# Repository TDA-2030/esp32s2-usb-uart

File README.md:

# ESP32S2-USB-UART

USB to UART board by ESP32-S2

## Feature

- [x] USB to UART
- [x] PCB size: 30mm x 14mm
- [x] All output with ESD protection
- [x] 3 LEDs
- [x] LEDs to indicate UART signal
- [x] 3.3V output
- [x] Either USBA or Type-C plug
- [ ] Auto download for ESP series chips
- [ ] Wireless connecting

## Pin definition

| 1(TCK) | 10(TX) |
| ------ | ------ |
| 2(TDI) | 9(RX)  |
| 3(TDO) | 8(EN)  |
| 4(TMS) | 7(IO0) |
| 5(3V3) | 6(GND) |

## Preview image

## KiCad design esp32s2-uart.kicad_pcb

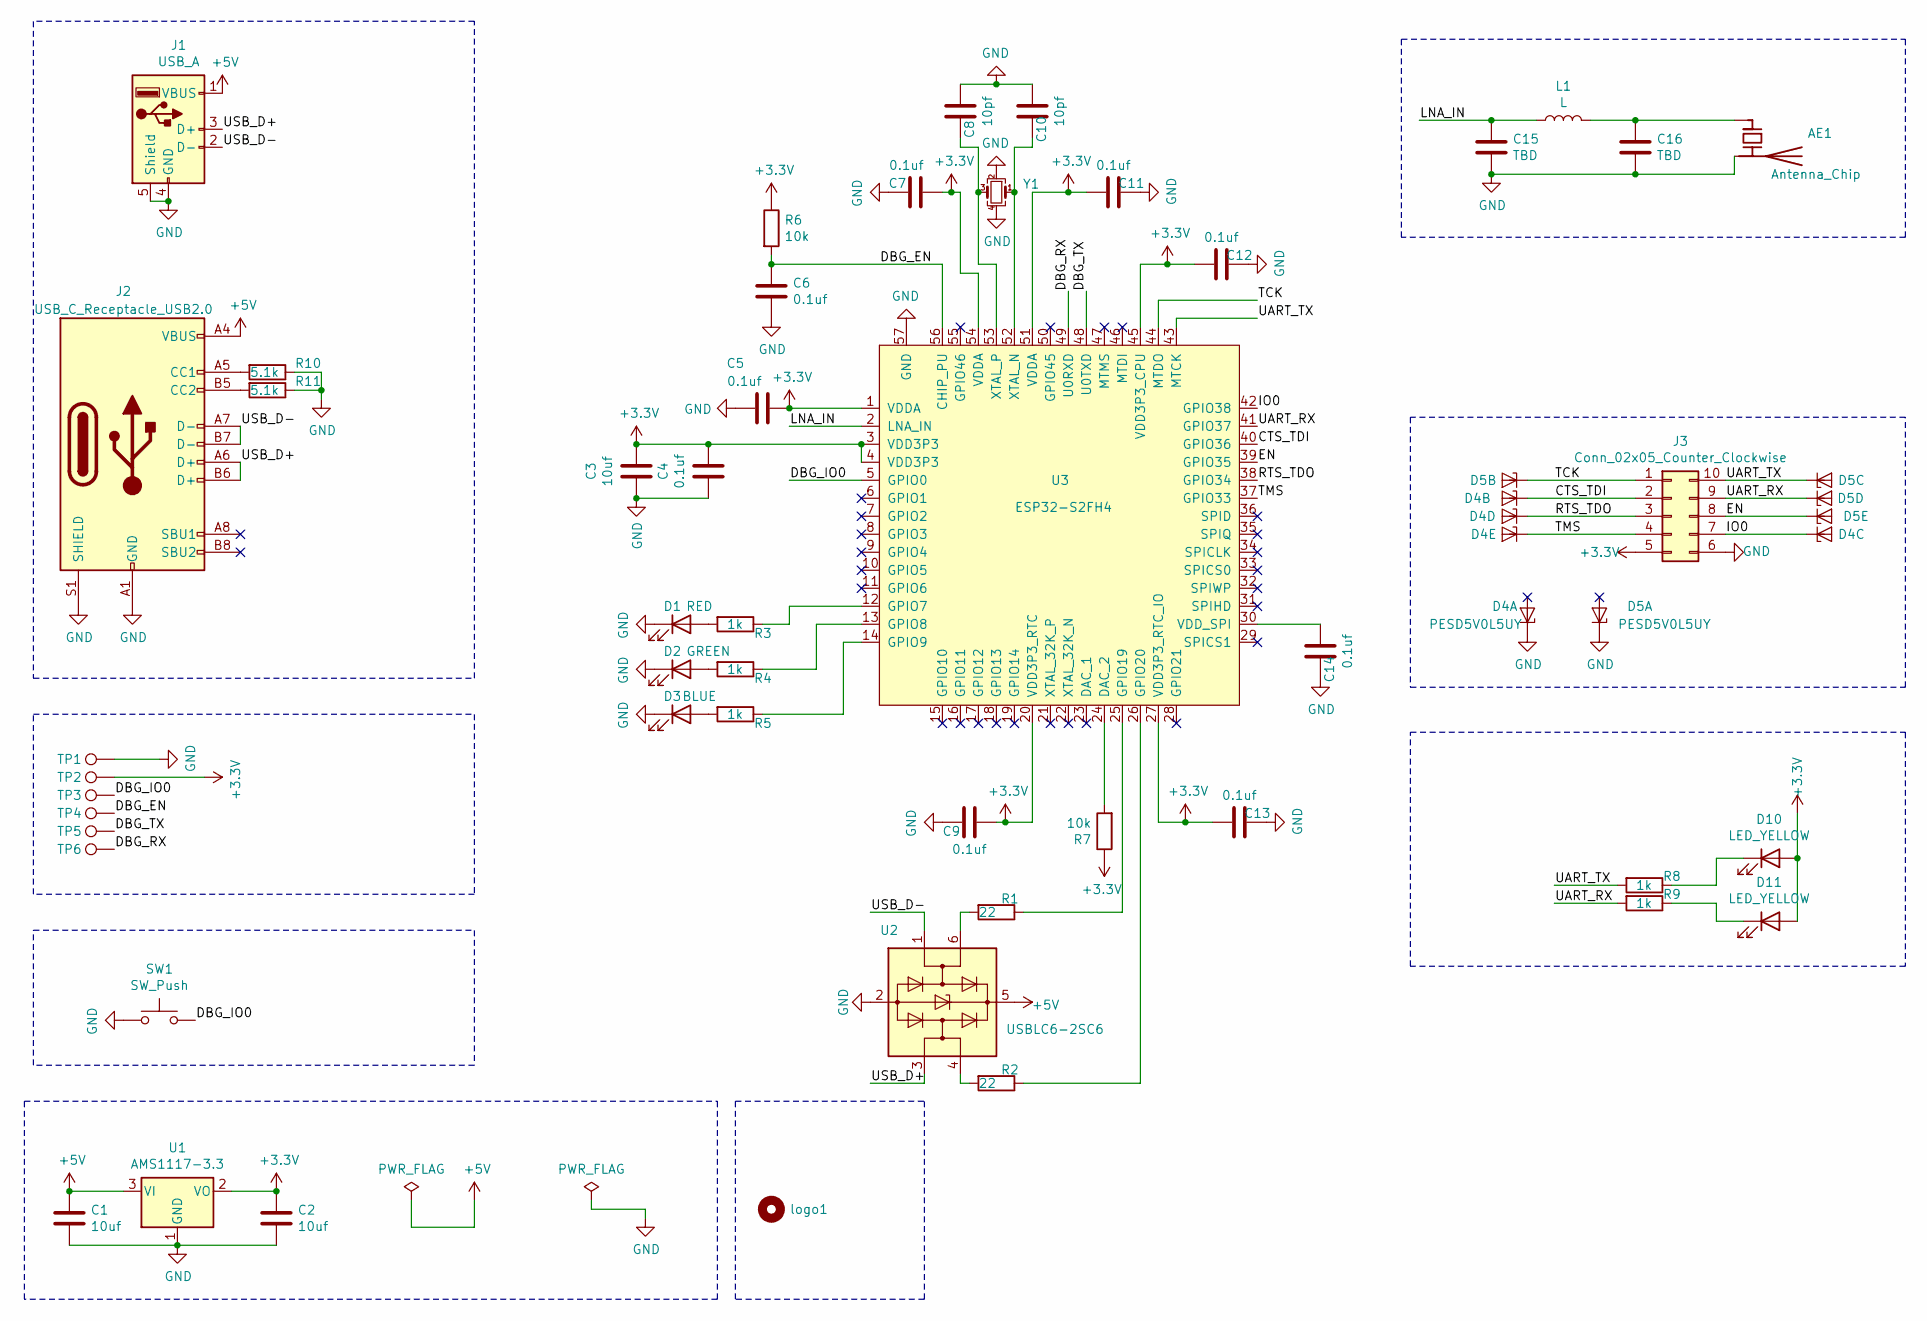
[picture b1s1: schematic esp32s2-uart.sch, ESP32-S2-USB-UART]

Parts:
AE1: Antenna_Chip; Johanson_2450AT43F0100
C1, C2, C3: 10uf; C_0603_1608Metric
C4, C5, C6, C7, C9, C11, C12, C13, C14: 0.1uf; C_0402_1005Metric
C8, C10: 10pf; C_0402_1005Metric
C15, C16: TBD; C_0402_1005Metric
D1: RED; LED_0603_1608Metric
D2: GREEN; LED_0603_1608Metric
D3: BLUE; LED_0603_1608Metric
D4, D5: PESD5V0L5UY; SOT-363_SC-70-6
D10, D11: LED_YELLOW; LED_0603_1608Metric
J1: USB_A; USB_A_CNCTech_1001-011-01101_Horizontal
J2: USB_C_Receptacle_USB2.0; USB_C_Receptacle
J3: Conn_02x05_Counter_Clockwise; Header_2x5_pin
L1: L; L_0402_1005Metric
R1, R2: 22; R_0402_1005Metric
R3, R4, R5, R8, R9: 1k; R_0402_1005Metric
R6, R7: 10k; R_0402_1005Metric
R10, R11: 5.1k; R_0402_1005Metric
SW1: SW_Push; button
TP1, TP2, TP3, TP4, TP5, TP6: TestPoint; TestPoint_Pad_D1.0mm
U1: AMS1117-3.3; SOT-223-3_TabPin2
U2: USBLC6-2SC6; SOT-23-6
U3: ESP32-S2FH4; QFN-56-1EP_7x7mm_P0.4mm_EP5.6x5.6mm
Y1: Crystal_GND24_Small; Crystal_SMD_EuroQuartz_MT-4Pin_3.2x2.5mm
logo1: logo; ESP-USB-Bridge

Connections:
+3V3: C2.2, C3.1, C4.1, C5.1, C7.1, C9.2, C11.2, C12.2, C13.2, D10.2 (A), D11.2 (A), J3.5, R6.1, R7.1, TP2.1, U1.2 (VO), U3.1 (VDDA), U3.3 (VDD3P3), U3.4 (VDD3P3), U3.20 (VDD3P3_RTC), U3.27 (VDD3P3_RTC_IO), U3.45 (VDD3P3_CPU), U3.51 (VDDA), U3.54 (VDDA)
+5V: C1.2, J1.1 (VBUS), J2.A4 (VBUS), J2.A9 (VBUS), J2.B4 (VBUS), J2.B9 (VBUS), U1.3 (VI), U2.5 (VBUS)
/CTS_TDI: D4.3 (K2), J3.2, U3.40 (GPIO36)
/DBG_EN: C6.1, R6.2, TP4.1, U3.56 (CHIP_PU)
/DBG_IO0: SW1.2, TP3.1, U3.5 (GPIO0)
/DBG_RX: TP6.1, U3.49 (U0RXD)
/DBG_TX: TP5.1, U3.48 (U0TXD)
/EN: D5.6 (K5), J3.8, U3.39 (GPIO35)
/IO0: D4.4 (K3), J3.7, U3.42 (GPIO38)
/LNA_IN: C15.1, L1.1, U3.2 (LNA_IN)
/RTS_TDO: D4.5 (K4), J3.3, U3.38 (GPIO34)
/TCK: D5.3 (K2), J3.1, U3.44 (MTDO)
/TMS: D4.6 (K5), J3.4, U3.37 (GPIO33)
/UART_RX: D5.5 (K4), J3.9, R9.2, U3.41 (GPIO37)
/UART_TX: D5.4 (K3), J3.10, R8.2, U3.43 (MTCK)
/USB_D+: J1.3 (D+), J2.A6 (D+), J2.B6 (D+), U2.3 (I/O2)
/USB_D-: J1.2 (D-), J2.A7 (D-), J2.B7 (D-), U2.1 (I/O1)
GND: AE1.2 (PCB_Trace), C1.1, C2.1, C3.2, C4.2, C5.2, C6.2, C7.2, C8.2, C9.1, C10.2, C11.1, C12.1, C13.1, C14.1, C15.2, C16.2, D1.1 (K), D2.1 (K), D3.1 (K), D4.1 (K1), D5.1 (K1), J1.4 (GND), J1.5 (Shield), J2.A1 (GND), J2.A12 (GND), J2.B1 (GND), J2.B12 (GND), J2.S1 (SHIELD), J3.6, R10.1, R11.1, SW1.1, TP1.1, U1.1 (GND), U2.2 (GND), U3.57 (GND), Y1.2, Y1.4
unnamed: AE1.1 (FEED), C16.1, L1.2
unnamed: C8.1, U3.53 (XTAL_P), Y1.3
unnamed: C10.1, U3.52 (XTAL_N), Y1.1
unnamed: C14.2, U3.30 (VDD_SPI)
unnamed: D1.2 (A), R3.2
unnamed: D2.2 (A), R4.2
unnamed: D3.2 (A), R5.2
unnamed: D10.1 (K), R8.1
unnamed: D11.1 (K), R9.1
unnamed: J2.A5 (CC1), R10.2
unnamed: J2.B5 (CC2), R11.2
unnamed: R1.1, U3.25 (GPIO19)
unnamed: R1.2, U2.6 (I/O1)
unnamed: R2.1, U3.26 (GPIO20)
unnamed: R2.2, U2.4 (I/O2)
unnamed: R3.1, U3.12 (GPIO7)
unnamed: R4.1, U3.13 (GPIO8)
unnamed: R5.1, U3.14 (GPIO9)
unnamed: R7.2, U3.24 (DAC_2)

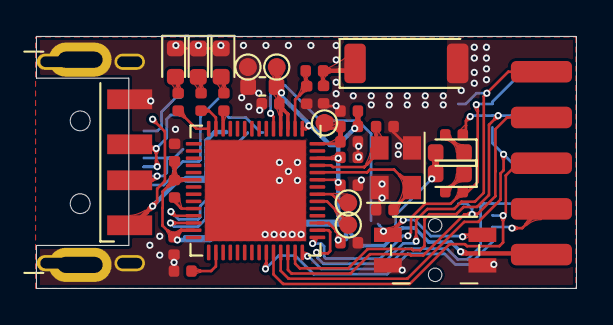
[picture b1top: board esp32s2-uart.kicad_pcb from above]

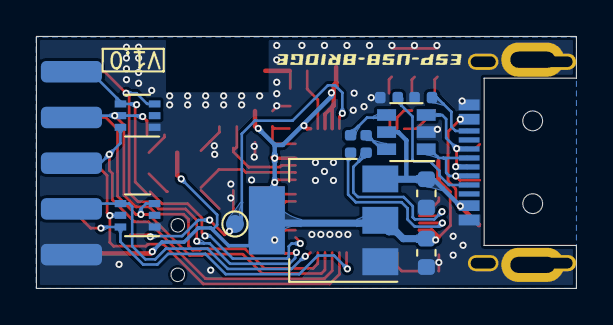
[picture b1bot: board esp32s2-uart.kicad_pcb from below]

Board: 2 copper layers, 30.0 x 14.0 mm, 51 parts (13 on the bottom side), 37 nets.

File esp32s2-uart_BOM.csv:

"Comment","Description","Designator","Footprint","LibRef","Pins","Quantity","PartNumber","url",
"10uf","desc","C3,","C_0603_1608Metric","libref","2","1","","",
"0.1uf","desc","C4,C5,C6,C7,C9,C11,C12,C13,C14,","C_0402_1005Metric","libref","2","9","","",
"10pf","desc","C8,C10,","C_0402_1005Metric","libref","2","2","","",
"TBD","desc","C15,C16,","C_0402_1005Metric","libref","2","2","","",
"RED","desc","D1,","LED_0603_1608Metric","libref","2","1","","",
"GREEN","desc","D2,","LED_0603_1608Metric","libref","2","1","","",
"BLUE","desc","D3,","LED_0603_1608Metric","libref","2","1","","",
"LED_YELLOW","desc","D10,D11,","LED_0603_1608Metric","libref","2","2","","",
"Conn_02x05_Counter_Clockwise","desc","J3,","Header_2x5_pin","libref","10","1","","",
"L","desc","L1,","L_0402_1005Metric","libref","2","1","","",
"1k","desc","R3,R4,R5,R8,R9,","R_0402_1005Metric","libref","2","5","","",
"10k","desc","R6,R7,","R_0402_1005Metric","libref","2","2","","",
"ESP32-S2FH4","desc","U3,","QFN-56-1EP_7x7mm_P0.4mm_EP5.6x5.6mm","libref","73","1","","",
"Crystal_GND24_Small","desc","Y1,","Crystal_SMD_EuroQuartz_MT-4Pin_3.2x2.5mm","libref","4","1","","",
"Antenna_Chip","desc","AE1,","Johanson_2450AT43F0100","libref","2","1","","",
"TestPoint","desc","TP1,TP2,TP4,TP5,TP6,","TestPoint_Pad_D1.0mm","libref","1","5","","",
"10uf","desc","C1,C2,","C_0603_1608Metric","libref","2","2","","",
"PESD5V0L5UY","desc","D4,D5,","SOT-363_SC-70-6","libref","6","2","","",
"22","desc","R1,R2,","R_0402_1005Metric","libref","2","2","","",
"5.1k","desc","R10,R11,","R_0402_1005Metric","libref","2","2","","",
"AMS1117-3.3","desc","U1,","SOT-223-3_TabPin2","libref","4","1","","",
"USBLC6-2SC6","desc","U2,","SOT-23-6","libref","6","1","","",
"TestPoint","desc","TP3,","TestPoint_Pad_D1.0mm","libref","1","1","","",
"logo","desc","logo1,","ESP-USB-Bridge","libref","0","1","","",
"Through Hole Items ",
"USB_A","desc","J1,","USB_A_CNCTech_1001-011-01101_Horizontal","libref","8","1","","",
"SW_Push","desc","SW1,","button","libref","6","1","","",
"USB_C_Receptacle_USB2.0","desc","J2,","USB_C_Receptacle","libref","20","1","","",

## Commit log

2021-03-25 updata
2021-03-26 add esp32-s2fh4 symbol lib
2021-03-29 complete schematic
2022-01-15 v1.0
2022-01-17 add type-c pull-down resistors
